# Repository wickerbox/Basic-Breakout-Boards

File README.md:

# Basic-Breakout-Boards

This is a collection of KiCad projects containing breakout boards that will be or have been designed, laid out, assembled, and tested. They are based on wickerlib, so to use them you can grab the <a href="https://github.com/wickerbox/wickerlib">wickerlib</a> symbols and footprints, and you'll be all set.

All the work here is released under the CERN Open Hardware License v1.2.

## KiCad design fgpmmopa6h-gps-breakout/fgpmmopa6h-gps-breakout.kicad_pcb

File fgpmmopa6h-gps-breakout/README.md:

<!--- start title --->
# FGPMMOPA6H GPS Breakout Board v1.1
Simple breakout board for the FGPMMOPA6H GPS module

Updated: 23 Feb 2017

- Author: Jenner Hanni
- Website: http://wickerbox.net
- Company: Wickerbox Electronics
- License: CERN Open Hardware License v1.2

<!--- end title --->

- To use with a 5V FTDI cable, orient cable with RESET (green) at pin 1 on J1.

- To use with 5V controllers, connect VCC, 5V_RX, 5V_TX, and GND.

- To use with 3.3V controllers, connect VCC, 5V_RX, 3.3V_TX, and GND.

1PPS, RTCM, and the FIX are 3.3V-level signals and may not be interpreted correctly by a 5V system.

### Notes on 3.3V/5V compatibility

- Atmega328 provides output signals above 4.2V for HIGH and below 0.9V for LOW. 
- Atmega328 detects input signals above 3V as HIGH and below 1.5V for LOW.
- The FGPMMOPA6H provides output signals 2.0-3.3V for HIGH and 0-0.8V for LOW. 
- The FGPMMOPA6H detects input signals 2.4-3.3V for HIGH and 0-0.4V for LOW.

<!--- bom start --->
### Bill of Materials

|Ref|Qty|Description|Digikey PN|
|---|---|-----------|------|
|AN1|1|CONN UFL JACK STR 50 OHM SMD|H122041-ND|
|BAT1|1|CR1220 BATTERY HOLDER SMT FLATPIN|BK-916-CT-ND|
|C3 C2 C1|3|CAP CER 1UF 10V X7R 0603|1276-1946-1-ND|
|C4|1|CAP CER 0.01UF 50V X7R 0603|490-1512-1-ND|
|D1|1|DIODE GEN PURP 75V 250MA 1N4148 SOD123|1655-1360-1-ND|
|J1|1|HEADER MALE 10POS TH 1x10 0.1”|952-1902-ND|
|LED1|1|LED AMBER DIFFUSED 0603 SMD|475-2712-1-ND|
|R1|1|RES SMD 10K OHM 1% 1/8W 0603|RNCP0603FTD10K0CT-ND|
|R3 R2|2|RES SMD 470 OHM 5% 1/4W 0603|RHM470DCT-ND|
|S1|1|SWITCH TACTILE SPST-NO 0.05A 12V|SW1020CT-ND|
|U1|1|IC REG LDO 3.3V 0.15A SOT353|576-3193-1-ND|

|Ref|Qty|Description|Adafruit PN|
|---|---|-----------|------|
|U2|1|GPS MODULE PA6H MTK3339|790|

<!--- bom end --->

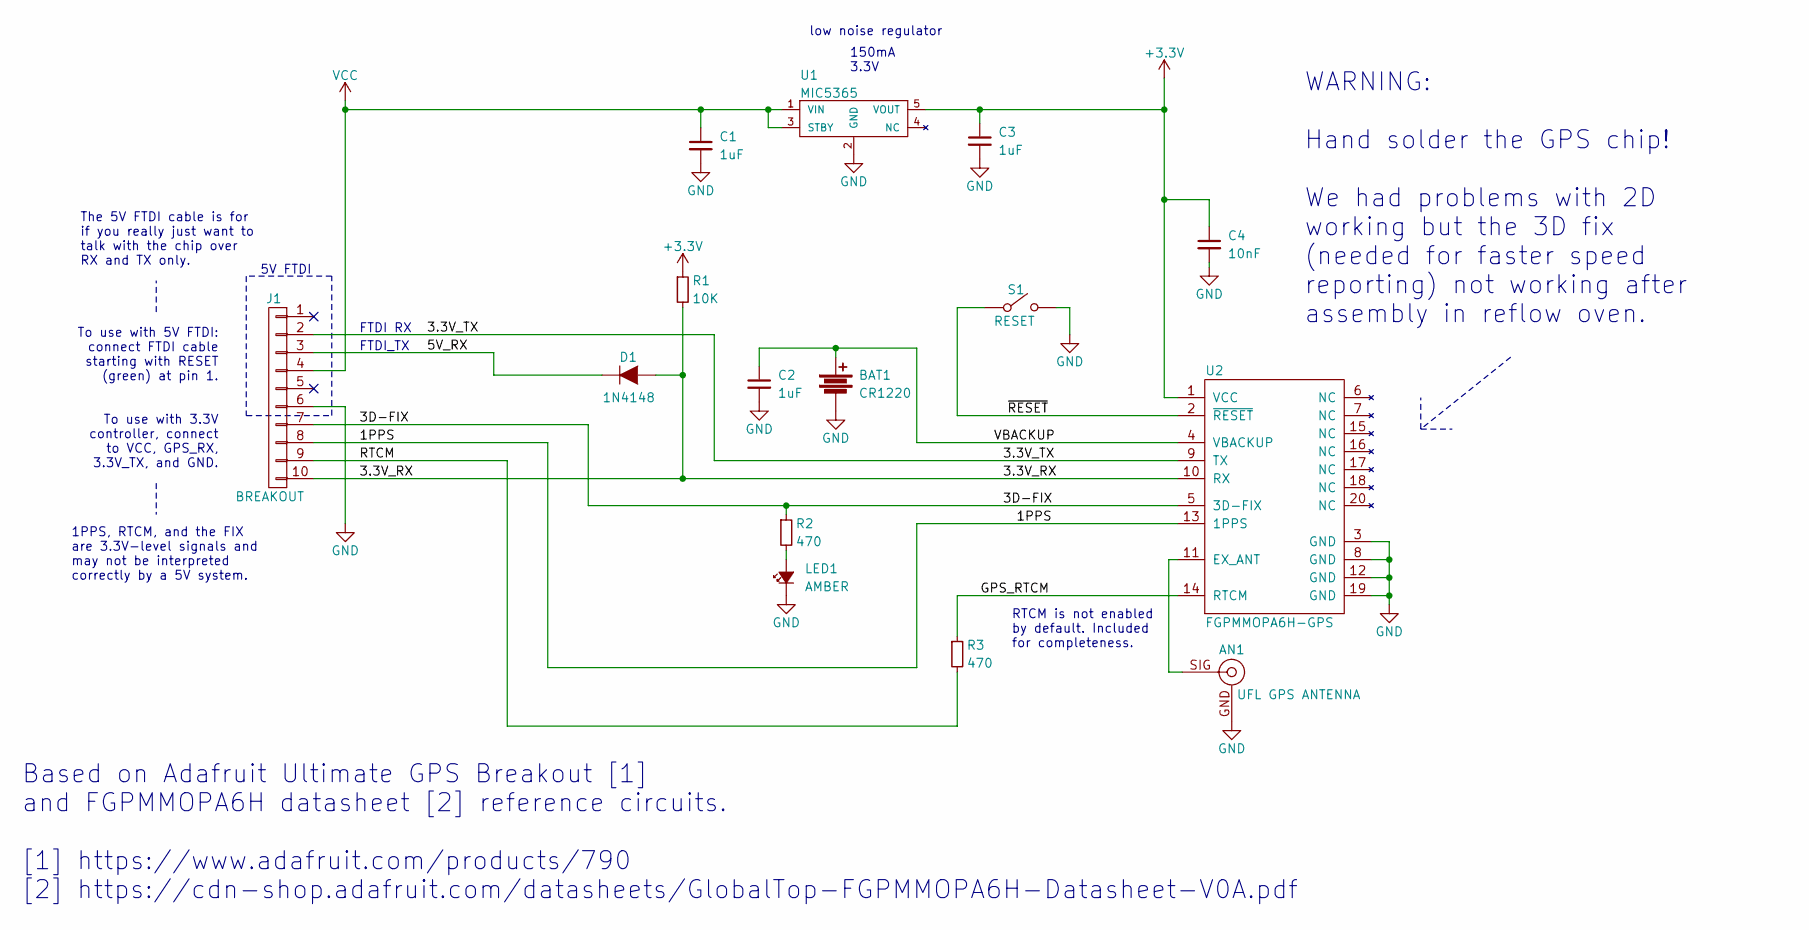
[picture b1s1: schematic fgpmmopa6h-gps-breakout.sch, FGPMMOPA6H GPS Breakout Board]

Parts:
AN1: UFL GPS ANTENNA; U.FL-COAX
BAT1: CR1220; BATT-HOLDER-CR1220-BK-916
C1, C2, C3: 1uF; RLC-0603-SMD
C4: 10nF; RLC-0603-SMD
D1: 1N4148; SOD-123
J1: BREAKOUT; CONN-HEADER-STRAIGHT-P2.54MM-1x10
LED1: AMBER; LED-0603-SMD
R1: 10K; RLC-0603-SMD
R2, R3: 470; RLC-0603-SMD
S1: RESET; SWITCH-OMRON-MOMENTARY-SMD-B3U-1000P
U1: MIC5365; SOT-353
U2: FGPMMOPA6H-GPS; FGPMMOPA6H

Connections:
+3V3: C3.1, C4.1, R1.1, U1.5 (VOUT), U2.1 (VCC)
/1PPS: J1.8, U2.13 (1PPS)
/3.3V_RX: D1.2 (A), J1.10, R1.2, U2.10 (RX)
/3.3V_TX: J1.2, U2.9 (TX)
/3D-FIX: J1.7, R2.1, U2.5 (3D-FIX)
/5V_RX: D1.1 (K), J1.3
/GPS_RTCM: R3.1, U2.14 (RTCM)
/RTCM: J1.9, R3.2
/VBACKUP: BAT1.1, C2.1, U2.4 (VBACKUP)
/~RESET: S1.1, U2.2 (~RESET)
GND: AN1.GND (2), BAT1.GND, C1.2, C2.2, C3.2, C4.2, J1.6, LED1.1 (K), S1.2, U1.2 (GND), U2.3 (GND), U2.8 (GND), U2.12 (GND), U2.19 (GND)
unnamed: AN1.SIG (1), U2.11 (EX_ANT)
unnamed: LED1.2 (A), R2.2
VCC: C1.1, J1.4, U1.1 (VIN), U1.3 (STBY)

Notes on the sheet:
150mA 3.3V
low noise regulator
Based on Adafruit Ultimate GPS Breakout [1] and FGPMMOPA6H datasheet [2] reference circuits. [1] https://www.adafruit.com/products/790 [2] https://cdn-shop.adafruit.com/datasheets/GlobalTop-FGPMMOPA6H-Datasheet-V0A.pdf
To use with 5V FTDI: connect FTDI cable starting with RESET (green) at pin 1. To use with 3.3V controller, connect to VCC, GPS_RX, 3.3V_TX, and GND.
RTCM is not enabled by default. Included for completeness.
1PPS, RTCM, and the FIX are 3.3V-level signals and may not be interpreted correctly by a 5V system.
The 5V FTDI cable is for if you really just want to talk with the chip over RX and TX only.
5V FTDI
FTDI RX
FTDI_TX
WARNING: Hand solder the GPS chip! We had problems with 2D working but the 3D fix (needed for faster speed reporting) not working after assembly in reflow oven.

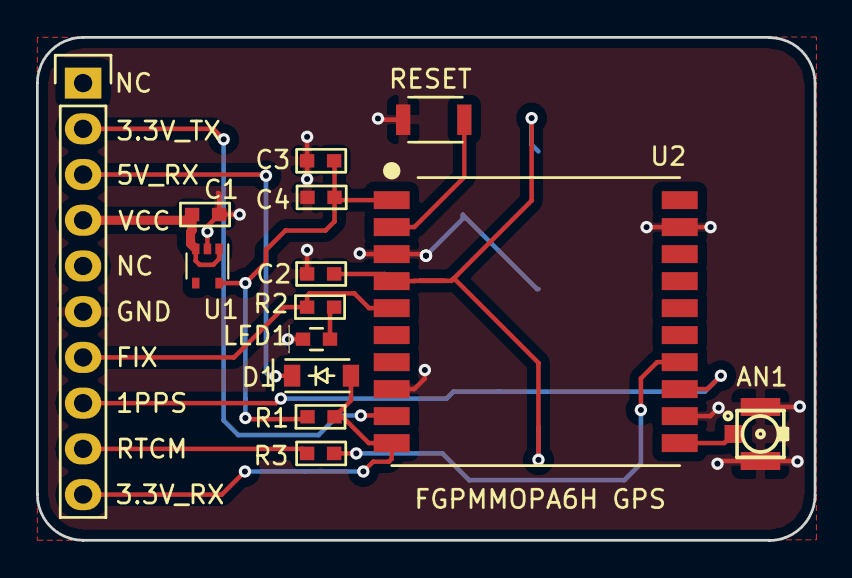
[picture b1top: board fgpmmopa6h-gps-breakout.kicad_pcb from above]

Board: 2 copper layers, 43.2 x 28.0 mm, 15 parts (1 on the bottom side), 14 nets.

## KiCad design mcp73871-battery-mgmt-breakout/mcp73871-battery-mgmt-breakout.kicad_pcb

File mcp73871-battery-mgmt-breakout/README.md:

<!--- start title --->
# MCP73871 Battery Management Breakout Board v1.0
Breakout board for a load-sharing battery/power control chip.

- Updated: 14 Aug 2017
- Author: Jenner Hanni
- Website: http://wickerbox.net
- Company: Wickerbox Electronics
- License: CERN Open Hardware License v1.2
<!--- end title --->

<!--- bom start --->
### Bill of Materials

|Ref|Qty|Description|Digikey PN|
|---|---|-----------|------|
|C1 C2 C3|3|CAP CER 4.7UF 50V X7R 1206|587-2994-1-ND|
|J1|1|USB MICRO-B RECEPTACLE 5PIN SMT R/A STUDS|609-4616-1-ND|
|J2|1|CONN HEADER PH SIDE 2POS 2MM|455-1719-ND|
|J3 J4|2|HEADER FEMALE 7POS TH 1x07 0.1IN|952-1905-ND|
|LED1 LED2 LED3|3|LED AMBER DIFFUSED 0603 SMD|475-2712-1-ND|
|R1|1|RES SMD 0.0 OHM JUMPER 1/8W 0603|MCT0603-0.0-ZZCT-ND|
|R2 R3 R4|3|RES SMD 470 OHM 5% 1/4W 0603|RHM470DCT-ND|
|R5|1|NTC THERMISTOR 10K OHM 1% 0402|445-2550-1-ND|
|R6|1|RES SMD 2K OHM 1% 1/8W 0603|RNCP0603FTD2K00CT-ND|
|R7|1|RES SMD 100K OHM 1% 1/10W 0603|RMCF0603FG100KCT-ND|
|U1|1|IC USB/AC BATT CHRGR MCP73871 20QFN|MCP73871T-2CCI/MLCT-ND|

|Ref|Qty|Description|Adafruit PN|
|---|---|-----------|------|
|B1|1|Lithium Ion Polymer Battery - 3.7v 500mAh|1578|

<!--- bom end --->
<!--- assy start --->
### Assembly Info for Quoting

<!--- assy end --->

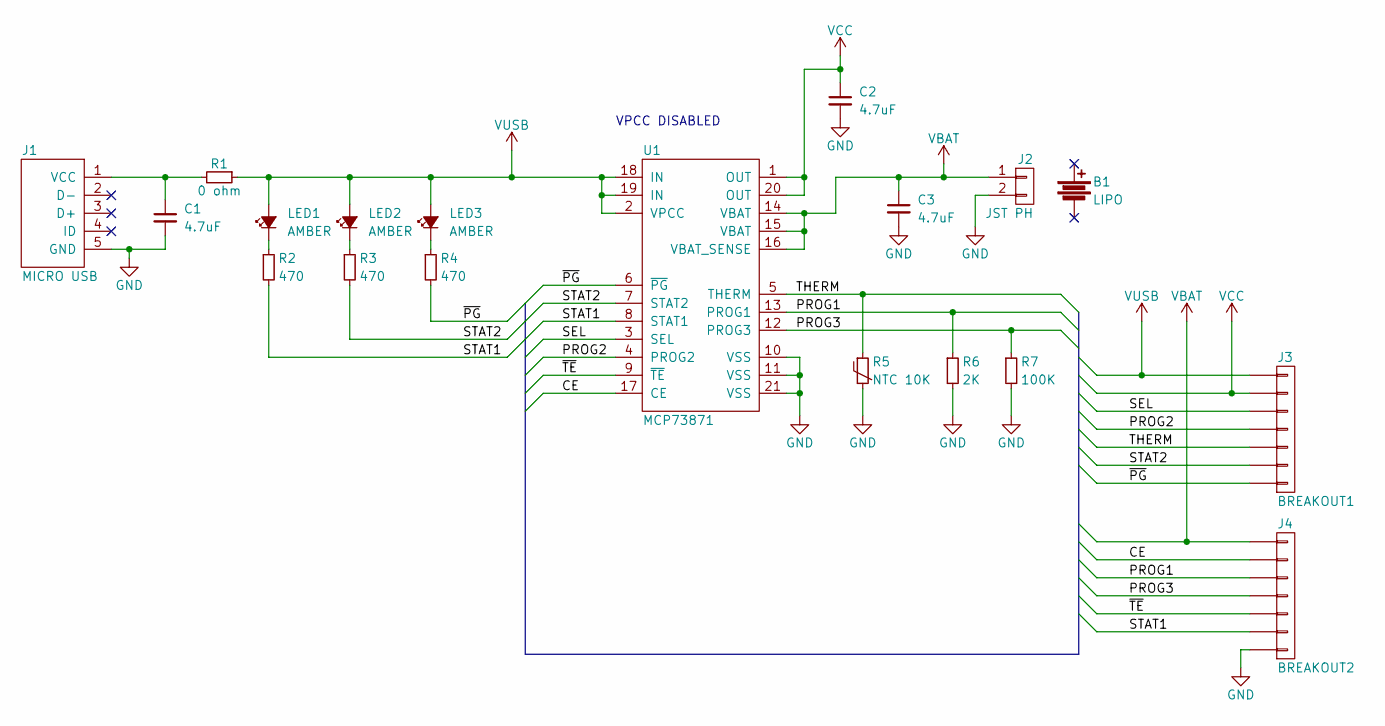
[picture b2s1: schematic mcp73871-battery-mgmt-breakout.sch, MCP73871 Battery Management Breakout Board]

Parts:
B1: LIPO; UNDEFINED
C1, C2, C3: 4.7uF; RLC-1206-SMD
J1: MICRO USB; CONN-USB-MICRO-B-AMPHENOL-10118193-0001LF
J2: JST PH; CONN-JST-S2B-PH-SM4-TB
J3: BREAKOUT1; CONN-HEADER-STRAIGHT-P2.54MM-1x07
J4: BREAKOUT2; CONN-HEADER-STRAIGHT-P2.54MM-1x07
LED1, LED2, LED3: AMBER; LED-0603-SMD
R1: 0 ohm; RLC-0603-SMD
R2, R3, R4: 470; RLC-0603-SMD
R5: NTC 10K; RLC-0402-SMD
R6: 2K; RLC-0603-SMD
R7: 100K; RLC-0603-SMD
U1: MCP73871; QFN-20-1EP-4x4MM_P0.5MM

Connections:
/CE: J4.2, U1.17 (CE)
/PROG1: J4.3, R6.1, U1.13 (PROG1)
/PROG2: J3.4, U1.4 (PROG2)
/PROG3: J4.4, R7.1, U1.12 (PROG3)
/SEL: J3.3, U1.3 (SEL)
/STAT1: J4.6, R2.2, U1.8 (STAT1)
/STAT2: J3.6, R3.2, U1.7 (STAT2)
/THERM: J3.5, R5.1, U1.5 (THERM)
/~PG: J3.7, R4.2, U1.6 (~PG)
/~TE: J4.5, U1.9 (~TE)
GND: C1.2, C2.2, C3.2, J1.5 (GND), J2.2, J4.7, R5.2, R6.2, R7.2, U1.10 (VSS), U1.11 (VSS), U1.21 (VSS)
unnamed: C1.1, J1.1 (VCC), R1.2
unnamed: LED1.1 (K), R2.1
unnamed: LED2.1 (K), R3.1
unnamed: LED3.1 (K), R4.1
VBAT: C3.1, J2.1, J4.1, U1.14 (VBAT), U1.15 (VBAT), U1.16 (VBAT_SENSE)
VCC: C2.1, J3.2, U1.1 (OUT), U1.20 (OUT)
VUSB: J3.1, LED1.2 (A), LED2.2 (A), LED3.2 (A), R1.1, U1.2 (VPCC), U1.18 (IN), U1.19 (IN)

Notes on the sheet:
VPCC DISABLED

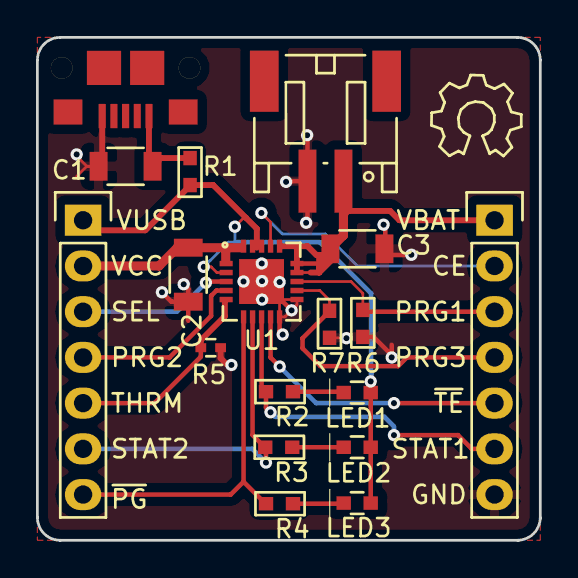
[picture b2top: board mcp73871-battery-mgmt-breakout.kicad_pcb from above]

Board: 2 copper layers, 27.9 x 27.9 mm, 18 parts (0 on the bottom side), 18 nets.

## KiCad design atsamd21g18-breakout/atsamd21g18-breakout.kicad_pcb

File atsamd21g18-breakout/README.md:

<!--- start title --->
# ATSAMD21G18 Cortex M0 Breakout Board v1.0
Arduino-compatible, breadboard-compatible with onboard uSD and RTC.

- Updated: 14 Aug 2017

- Author: Jenner Hanni
- Website: http://wickerbox.net
- Company: Wickerbox Electronics
- License: CERN Open Hardware License v1.2
<!--- end title --->

Comes with a 5-pin SWD programming interface so the bootloader can be flashed using an STLink v2 and [adalink](https://github.com/adafruit/Adafruit_Adalink).

<!--- bom start --->
### Bill of Materials

|Ref|Qty|Description|Digikey PN|
|---|---|-----------|------|
|C1 C2 C5|3|CAP CER 1UF 25V X7R 0603|587-2984-1-ND|
|C10 C11 C4 C7 C9|5|CAP CER 0.1UF 100V X7R 0603|490-3285-1-ND|
|C3|1|CAP CER 10UF 16V X7R 0805|1276-2872-1-ND|
|C6 C8|2|CAP CER 22pF 50V NP0 0603|399-9031-1-ND|
|D1 D3|2|VARISTOR ESD PROTECT USB|CG0603MLC-05ECT-ND|
|D2|1|DIODE SCHOTTKY 20V 1A SMA|SS12-E3/61TGICT-ND|
|J1|1|HEADER MALE 5POS TH 1x05 0.1IN|952-1902-ND|
|J2|1|USB MICRO-B RECEPTACLE 5PIN SMT R/A STUDS|609-4616-1-ND|
|J3 J4|2|HEADER FEMALE 18POS TH 1x18 0.1IN|952-1905-ND|
|L1 L2 L3|3|FERRITE BEAD 30 OHM 0805 1LN|MH2029-300YCT-ND|
|R1|1|RES SMD 1K OHM 1% 1/10W 0603|1276-3484-1-ND|
|R2|1|RES SMD 10K OHM 1% 1/8W 0603|RNCP0603FTD10K0CT-ND|
|R3|1|RES SMD 330 OHM 5% 1/10W 0603|311-330GRCT-ND|
|S1|1|SWITCH TACTILE SPST-NO 0.05A 12V|SW1020CT-ND|
|U1|1|IC REG LDO 3.3V 0.5A BU33SD5WG 5SSOP|BU33SD5WG-TRCT-ND|
|U2|1|IC MCU 32BIT 256KB FLASH ATSAMD21G 48TQFP|ATSAMD21G18A-AUTCT-ND|
|X1|1|CRYSTAL 16MHZ 30PPM 18pF 4SMD|CTX1206CT-ND|

<!--- bom end --->

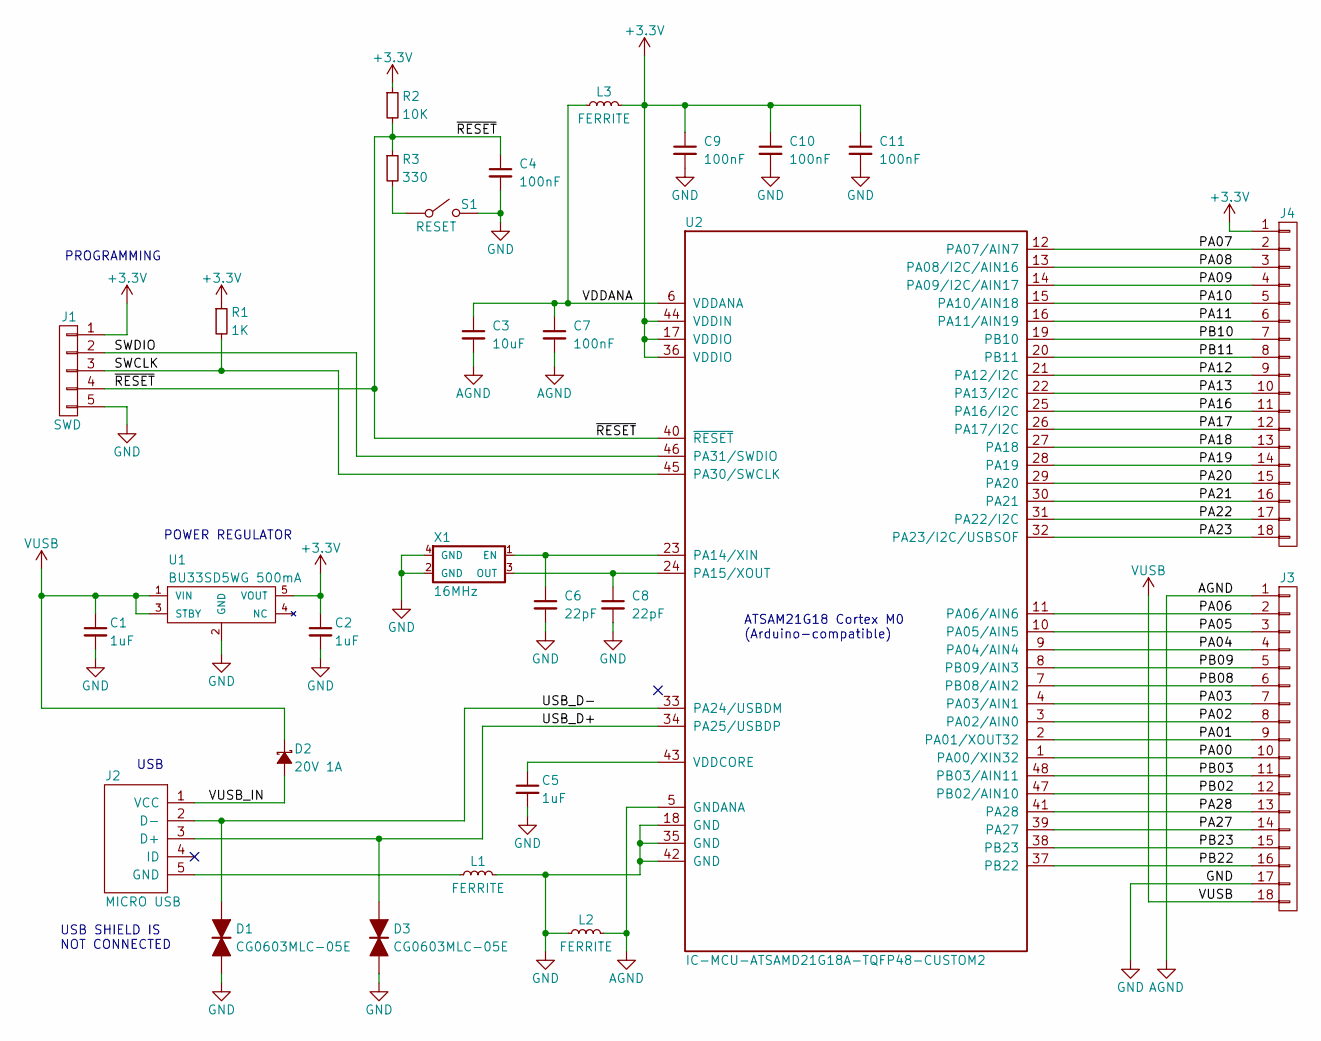
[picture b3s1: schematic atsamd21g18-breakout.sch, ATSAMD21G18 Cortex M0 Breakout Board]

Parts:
C1, C2, C5: 1uF; RLC-0603-SMD
C3: 10uF; RLC-0805-SMD
C4, C7, C9, C10, C11: 100nF; RLC-0603-SMD
C6, C8: 22pF; RLC-0603-SMD
D1, D3: CG0603MLC-05E; RLC-0603-SMD
D2: 20V 1A; DIODE-SMA
J1: SWD; CONN-HEADER-STRAIGHT-P2.54MM-1x05
J2: MICRO USB; CONN-USB-MICRO-B-AMPHENOL-10118193-0001LF
J3, J4: HEADER-FEMALE-18POS-TH-1x18-P0.1IN; CONN-HEADER-STRAIGHT-P2.54MM-1x18
L1, L2, L3: FERRITE; RLC-0805-SMD
R1: 1K; RLC-0603-SMD
R2: 10K; RLC-0603-SMD
R3: 330; RLC-0603-SMD
S1: RESET; SWITCH-OMRON-MOMENTARY-SMD-B3U-1000P
U1: BU33SD5WG 500mA; SSOP-5
U2: IC-MCU-ATSAMD21G18A-TQFP48-CUSTOM2; TQFP-48_7x7mm_Pitch0.5mm
X1: 16MHz; CRYSTAL-CTS-4SMD

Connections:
+3V3: C2.1, C9.1, C10.1, C11.1, J1.1, J4.1, L3.2, R1.1, R2.1, U1.5 (VOUT), U2.17 (VDDIO), U2.36 (VDDIO), U2.44 (VDDIN)
/PA00: J3.10, U2.1 (PA00/XIN32)
/PA01: J3.9, U2.2 (PA01/XOUT32)
/PA02: J3.8, U2.3 (PA02/AIN0)
/PA03: J3.7, U2.4 (PA03/AIN1)
/PA04: J3.4, U2.9 (PA04/AIN4)
/PA05: J3.3, U2.10 (PA05/AIN5)
/PA06: J3.2, U2.11 (PA06/AIN6)
/PA07: J4.2, U2.12 (PA07/AIN7)
/PA08: J4.3, U2.13 (PA08/I2C/AIN16)
/PA09: J4.4, U2.14 (PA09/I2C/AIN17)
/PA10: J4.5, U2.15 (PA10/AIN18)
/PA11: J4.6, U2.16 (PA11/AIN19)
/PA12: J4.9, U2.21 (PA12/I2C)
/PA13: J4.10, U2.22 (PA13/I2C)
/PA16: J4.11, U2.25 (PA16/I2C)
/PA17: J4.12, U2.26 (PA17/I2C)
/PA18: J4.13, U2.27 (PA18)
/PA19: J4.14, U2.28 (PA19)
/PA20: J4.15, U2.29 (PA20)
/PA21: J4.16, U2.30 (PA21)
/PA22: J4.17, U2.31 (PA22/I2C)
/PA23: J4.18, U2.32 (PA23/I2C/USBSOF)
/PA27: J3.14, U2.39 (PA27)
/PA28: J3.13, U2.41 (PA28)
/PB02: J3.12, U2.47 (PB02/AIN10)
/PB03: J3.11, U2.48 (PB03/AIN11)
/PB08: J3.6, U2.7 (PB08/AIN2)
/PB09: J3.5, U2.8 (PB09/AIN3)
/PB10: J4.7, U2.19 (PB10)
/PB11: J4.8, U2.20 (PB11)
/PB22: J3.16, U2.37 (PB22)
/PB23: J3.15, U2.38 (PB23)
/SWCLK: J1.3, R1.2, U2.45 (PA30/SWCLK)
/SWDIO: J1.2, U2.46 (PA31/SWDIO)
/USB_D+: D3.1, J2.3 (D+), U2.34 (PA25/USBDP)
/USB_D-: D1.1, J2.2 (D-), U2.33 (PA24/USBDM)
/VDDANA: C3.1, C7.1, L3.1, U2.6 (VDDANA)
/VUSB_IN: D2.2 (A), J2.1 (VCC)
/~RESET: C4.1, J1.4, R2.2, R3.1, U2.40 (~RESET)
AGND: C3.2, C7.2, J3.1, L2.2, U2.5 (GNDANA)
GND: C1.2, C2.2, C4.2, C5.2, C6.2, C8.2, C9.2, C10.2, C11.2, D1.2, D3.2, J1.5, J3.17, L1.2, L2.1, S1.2, U1.2 (GND), U2.18 (GND), U2.35 (GND), U2.42 (GND), X1.2 (GND), X1.4 (GND)
unnamed: C5.1, U2.43 (VDDCORE)
unnamed: C6.1, U2.23 (PA14/XIN), X1.1 (EN)
unnamed: C8.1, U2.24 (PA15/XOUT), X1.3 (OUT)
unnamed: J2.5 (GND), L1.1
unnamed: R3.2, S1.1
VUSB: C1.1, D2.1 (K), J3.18, U1.1 (VIN), U1.3 (STBY)

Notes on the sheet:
ATSAM21G18 Cortex M0 (Arduino-compatible)
PROGRAMMING
POWER REGULATOR
USB
USB SHIELD IS NOT CONNECTED

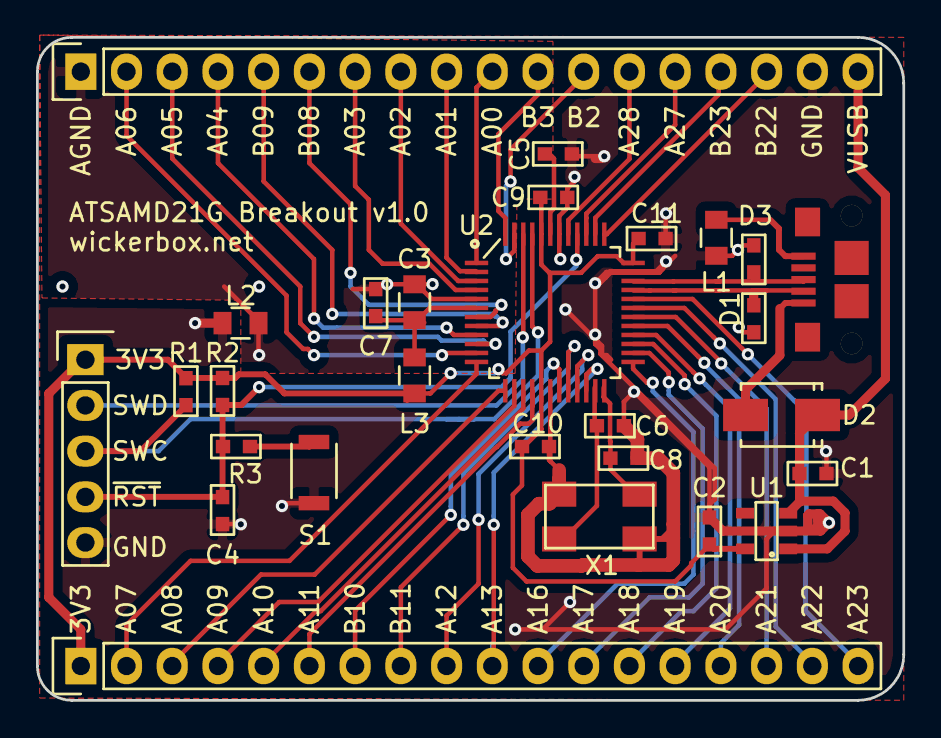
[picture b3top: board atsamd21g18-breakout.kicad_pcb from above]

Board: 2 copper layers, 48.1 x 36.8 mm, 28 parts (0 on the bottom side), 48 nets.

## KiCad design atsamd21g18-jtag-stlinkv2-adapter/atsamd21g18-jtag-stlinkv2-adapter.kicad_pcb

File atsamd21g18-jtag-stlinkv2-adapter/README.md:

<!--- start title --->
# ATSAMD21G18-STLinkv2 JTAG Adapter Board v1.0
Converts 20-pin giant JTAG connector into 1.27mm-pitch 2x5 connector.

- Updated: 14 Aug 2017

- Author: Jenner Hanni
- Website: http://wickerbox.net
- Company: Wickerbox Electronics
- License: CERN Open Hardware License v1.2
<!--- end title --->

Description.

<!--- bom start --->
### Bill of Materials

|Ref|Qty|Description|Digikey PN|
|---|---|-----------|------|
|J1|1|HEADER MALE 20POS TH 2x10 0.1IN KEY|ED10524-ND|
|J2|1|HEADER MALE SHROUDED 10POS 2x5 0.1IN KEY JTAG|30310-6002HB-ND|
|J3|1|HEADER MALE 5POS TH 1x05 0.1IN|952-1902-ND|
|J4|1|HEADER MALE SHROUDED 10POS 2x5 0.27MM KEY|1175-1627-ND|

<!--- bom end --->

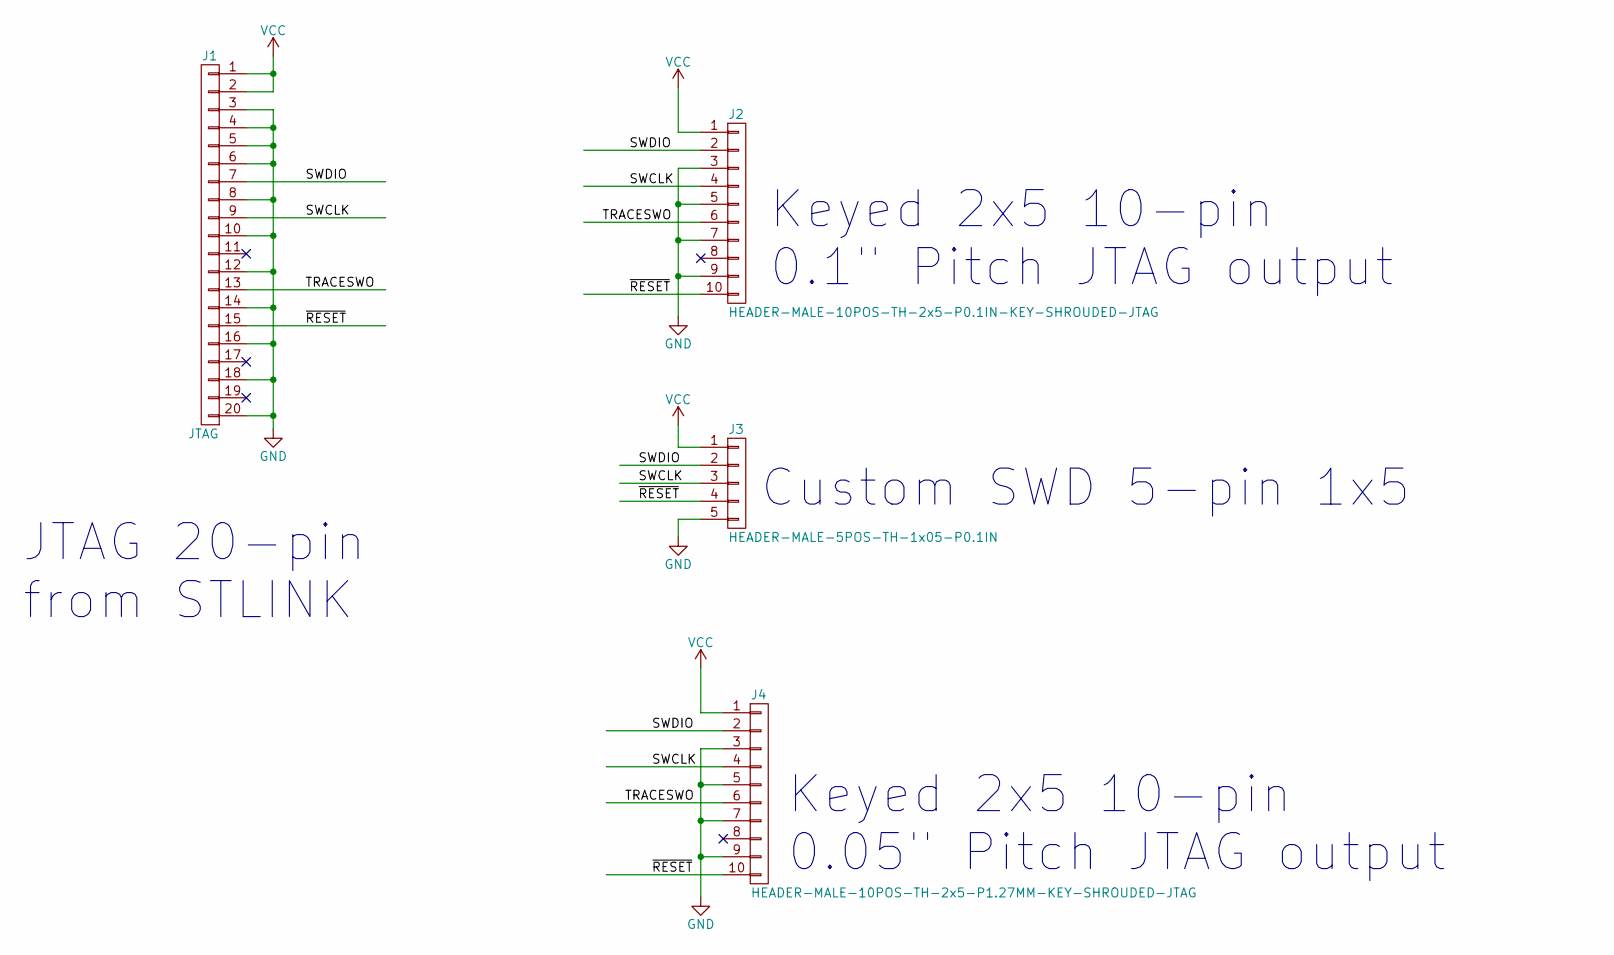
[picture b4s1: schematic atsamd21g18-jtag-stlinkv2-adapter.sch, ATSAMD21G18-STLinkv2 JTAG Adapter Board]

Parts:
J1: JTAG; CONN-ONSHORE-JTAG-2x10-2.54MMP
J2: HEADER-MALE-10POS-TH-2x5-P0.1IN-KEY-SHROUDED-JTAG; CONN-3M-JTAG-2x05-2.54MMP
J3: HEADER-MALE-5POS-TH-1x05-P0.1IN; CONN-HEADER-STRAIGHT-P2.54MM-1x05
J4: HEADER-MALE-10POS-TH-2x5-P1.27MM-KEY-SHROUDED-JTAG; CONN-ONSHORE-JTAG-2x05-1.27MMP

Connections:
/SWCLK: J1.9, J2.4, J3.3, J4.4
/SWDIO: J1.7, J2.2, J3.2, J4.2
/TRACESWO: J1.13, J2.6, J4.6
/~RESET: J1.15, J2.10, J3.4, J4.10
GND: J1.3, J1.4, J1.5, J1.6, J1.8, J1.10, J1.12, J1.14, J1.16, J1.18, J1.20, J2.3, J2.5, J2.7, J2.9, J3.5, J4.3, J4.5, J4.7, J4.9
VCC: J1.1, J1.2, J2.1, J3.1, J4.1

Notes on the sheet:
JTAG 20-pin from STLINK
Keyed 2x5 10-pin 0.1" Pitch JTAG output
Custom SWD 5-pin 1x5
Keyed 2x5 10-pin 0.05" Pitch JTAG output

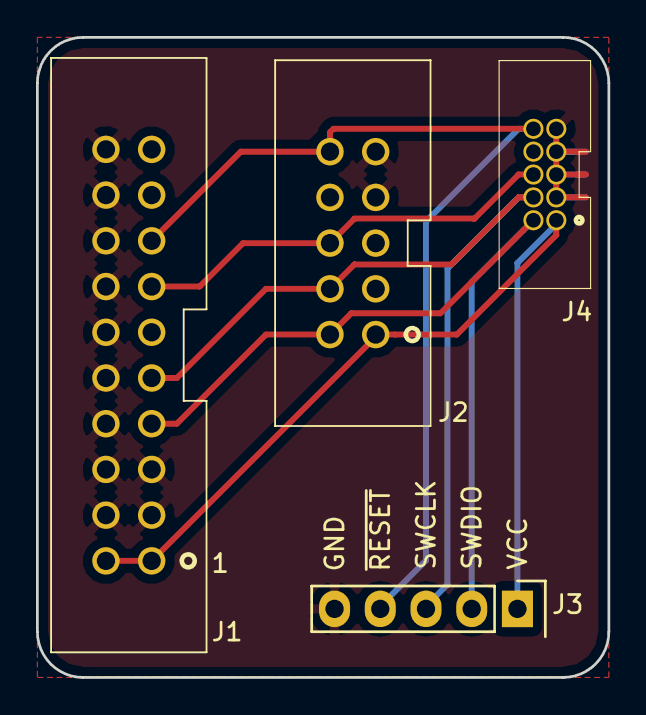
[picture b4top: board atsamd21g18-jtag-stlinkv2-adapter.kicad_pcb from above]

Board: 2 copper layers, 31.8 x 35.6 mm, 4 parts (0 on the bottom side), 6 nets.

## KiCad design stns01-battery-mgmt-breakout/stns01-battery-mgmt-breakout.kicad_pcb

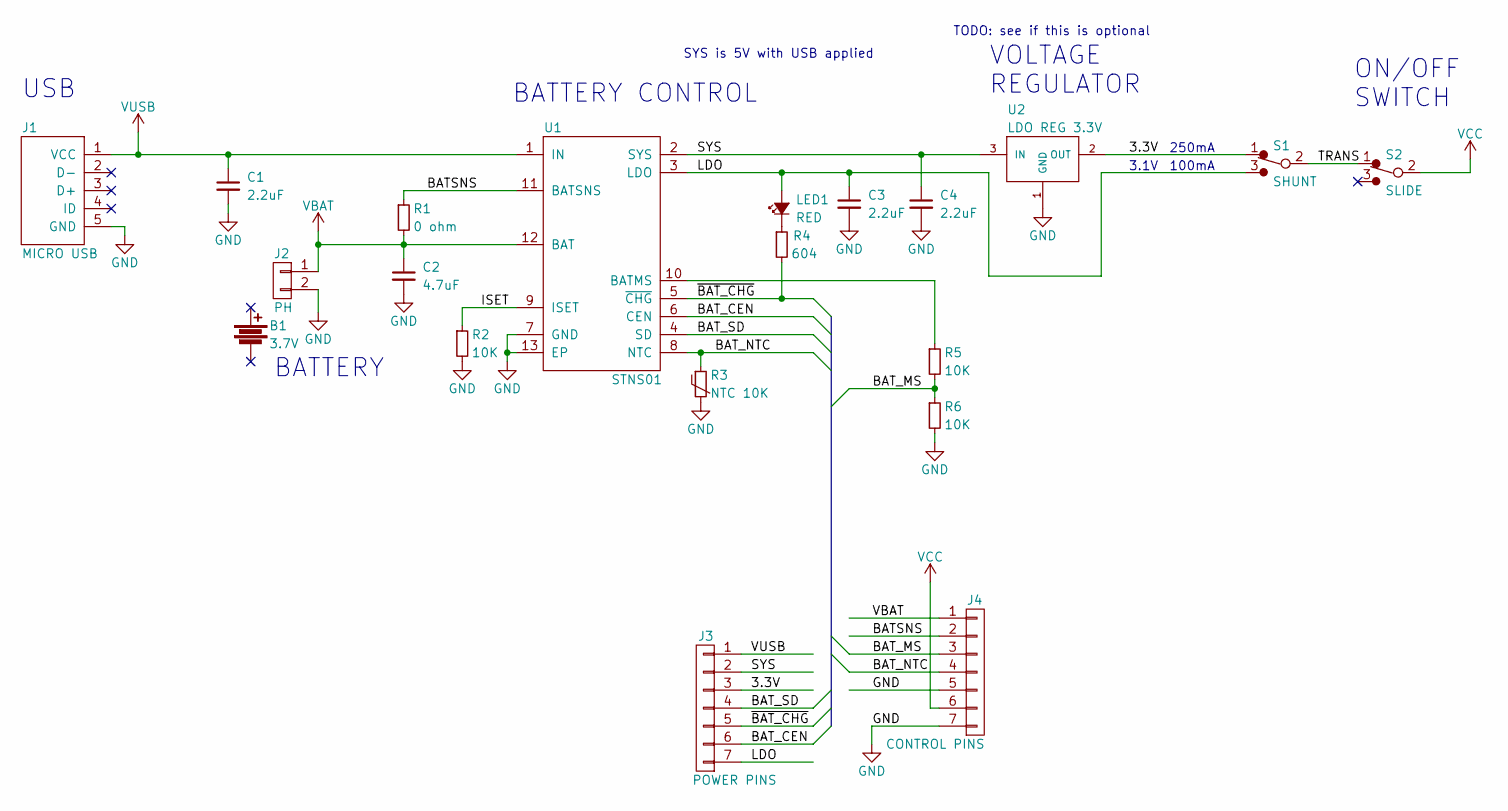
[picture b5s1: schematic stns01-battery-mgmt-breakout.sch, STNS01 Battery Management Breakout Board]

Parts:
B1: 3.7V; UNDEFINED
C1, C3, C4: 2.2uF; RLC-0603-SMD
C2: 4.7uF; RLC-0603-SMD
J1: MICRO USB; CONN-USB-MICRO-B-AMPHENOL-10118193-0001LF
J2: PH; CONN-JST-S2B-PH-SM4-TB
J3: POWER PINS; CONN-HEADER-STRAIGHT-P2.54MM-1x07
J4: CONTROL PINS; CONN-HEADER-STRAIGHT-P2.54MM-1x07
LED1: RED; LED-0603-SMD
R1: 0 ohm; RLC-0603-SMD
R2, R5, R6: 10K; RLC-0603-SMD
R3: NTC 10K; RLC-0603-SMD
R4: 604; RLC-0603-SMD
S1: SHUNT; CONN-HEADER-STRAIGHT-P2.54MM-1x03
S2: SLIDE; SWITCH-ESWITCH-SLIDE-TH-EG1218
U1: STNS01; DFN-12-1EP-3x3MM-P0.45MM
U2: LDO REG 3.3V; SOT-23-3

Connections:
/3.3V: J3.3, S1.1, U2.2 (OUT)
/BATSNS: J4.2, R1.1, U1.11 (BATSNS)
/BAT_CEN: J3.6, U1.6 (CEN)
/BAT_MS: J4.3, R5.2, R6.1
/BAT_NTC: J4.4, R3.1, U1.8 (NTC)
/BAT_SD: J3.4, U1.4 (SD)
/ISET: R2.1, U1.9 (ISET)
/LDO: C3.1, J3.7, LED1.2 (A), S1.3, U1.3 (LDO)
/SYS: C4.1, J3.2, U1.2 (SYS), U2.3 (IN)
/TRANS: S1.2, S2.1
/~BAT_CHG: J3.5, R4.2, U1.5 (~CHG)
GND: C1.2, C2.2, C3.2, C4.2, J1.5 (GND), J2.2, J4.5, J4.7, R2.2, R3.2, R6.2, U1.7 (GND), U1.13 (EP), U2.1 (GND)
unnamed: LED1.1 (K), R4.1
unnamed: R5.1, U1.10 (BATMS)
VBAT: C2.1, J2.1, J4.1, R1.2, U1.12 (BAT)
VCC: J4.6, S2.2
VUSB: C1.1, J1.1 (VCC), J3.1, U1.1 (IN)

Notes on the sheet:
BATTERY CONTROL
VOLTAGE REGULATOR
USB
250mA
100mA
BATTERY
SYS is 5V with USB applied
ON/OFF SWITCH
3.1V
TODO: see if this is optional

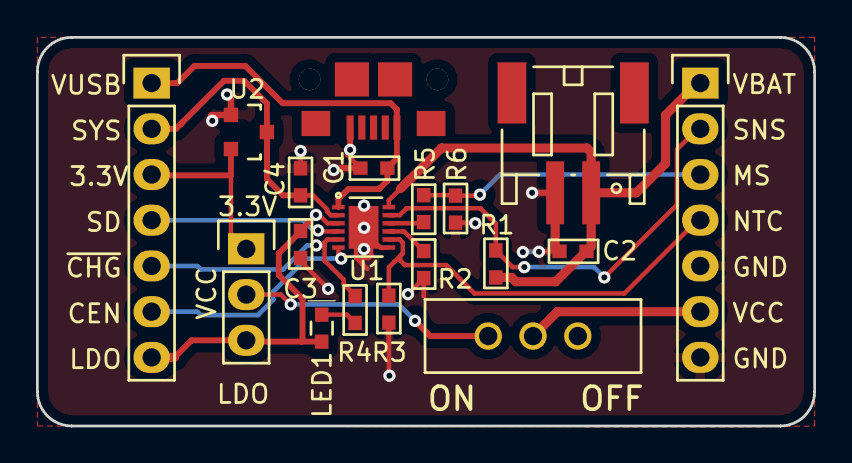
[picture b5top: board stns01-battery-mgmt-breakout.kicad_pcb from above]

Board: 2 copper layers, 43.2 x 21.6 mm, 19 parts (0 on the bottom side), 17 nets.

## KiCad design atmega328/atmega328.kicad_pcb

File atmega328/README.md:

<!--- start title --->
# Basic Atmega328 Breakout Board v1.2

This is a breakout board for the Atmega328. It supports input voltage up to 16V, regulating down to 5V for the microcontroller. A bootloader can be loaded over ICSP and then the board can be powered and communicated with over an FTDI cable. All the input/output pins are broken out for prototyping.

Updated: 31 Dec 2016

- Author: Jenner Hanni
- Website: http://wickerbox.net
- Company: Wickerbox Electronics
- License: CERN Open Hardware License v1.2
<!--- end title --->

The project is released as open hardware under the CERN v1.2 Open Hardware license.

<!--- start title --->
The project uses the Atmega328 template from [wickerlib](http://wickerbox.net/wickerlib).

You can order a set of three bare boards for $13.35 from OSH Park [here](https://oshpark.com/shared_projects/Bx0lZ6cN).
<!--- end title --->

### Bill of Materials

<!--- bom start --->
### Bill of Materials

|Ref|Qty|Description|Digikey PN|
|---|---|-----------|------|
|C2 C6|2|CAP CER 10UF 25V X7R 1210|587-2599-1-ND|
|C3 C4|2|CAP CER 22pF 100V C0G NP0 0603|399-11145-1-ND|
|C7 C8 C9 C1 C5|5|CAP CER 0.1UF 100V X7R 0603|490-3285-1-ND|
|D1|1|TVS DIODE 14VWM 23.2VC SMAJ14A-13-F SMA|SMAJ14A-FDICT-ND|
|D2 D3|2|DIODE SCHOTTKY 20V 1A SMA|SS12-E3/61TGICT-ND|
|F1|1|RESETTABLE FUSE 1.1A 25V MF-MSMF|MF-MSMF110/24X-2CT-ND|
|J1|1|CONN TERM SCREW GREEN 2.54MM 2POS TH|ED10561-ND|
|J2|1|HEADER MALE 6POS TH 1x06 0.1”|952-1902-ND|
|J3|1|HEADER MALE 6POS 2x3 0.1”|952-1921-ND|
|J4 J5|2|HEADER FEMALE 12POS TH 1x12 0.1”|952-1905-ND|
|JP1|1|SHUNT JUMPER 0.1IN BLACK GOLD|3M9580-ND|
|LED1|1|LED AMBER DIFFUSED 0603 SMD|475-2712-1-ND|
|R1|1|RES SMD 10K OHM 5% 1/8W 0805|311-10KARCT-ND|
|R2|1|RES SMD 220 OHM 5% 1/10W 0603|311-22GRCT-ND|
|S1|1|SWITCH TACTILE SPST-NO 0.05A 12V|SW1020CT-ND|
|U1|1|IC REG LDO 5V 1.1A NCP1117 DPAK| NCP1117DT50GOS-ND|
|U2|1|IC MCU 8BIT 32KB FLASH 32TQFP|ATMEGA328P-AU-ND|
|X1|1|CRYSTAL 16MHz 18pF 40 OHM 4SMD|CTX1206CT-ND|

<!--- bom end --->

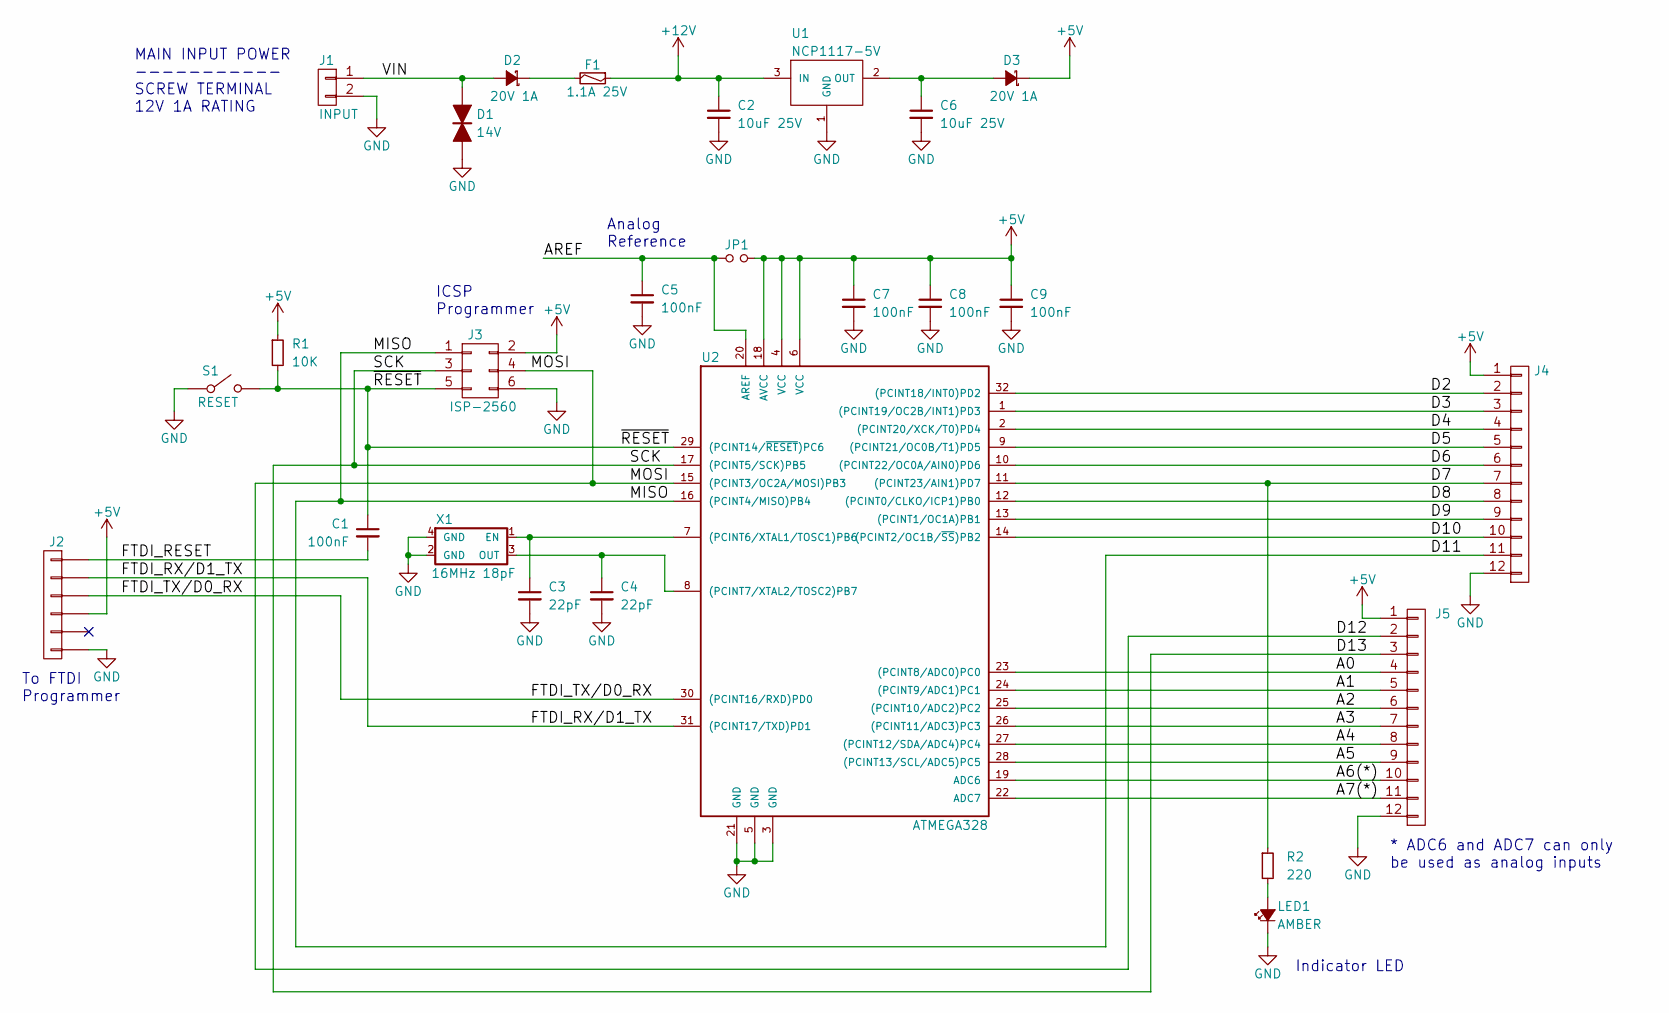
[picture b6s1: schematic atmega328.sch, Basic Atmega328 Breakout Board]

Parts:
C1, C5, C7, C8, C9: 100nF; RLC-0603-SMD
C2, C6: 10uF 25V; RLC-1210-SMD
C3, C4: 22pF; RLC-0603-SMD
D1: 14V; DIODE-SMA
D2, D3: 20V 1A; DIODE-SMA
F1: 1.1A 25V; RLC-1812-SMD
J1: INPUT; CONN-ONSHORE-SCREW-GREEN-2PIN-TH
J2: FTDI; CONN-HEADER-STRAIGHT-P2.54MM-1x06
J3: ISP-2560; CONN-HEADER-STRAIGHT-P2.54MM-2x03
J4, J5: HEADER-FEMALE-12POS-TH-1x12-P0.1IN; CONN-HEADER-STRAIGHT-P2.54MM-1x12
JP1: JUMP; CONN-HEADER-STRAIGHT-P2.54MM-1x02
LED1: AMBER; RLC-0603-SMD
R1: 10K; RLC-0805-SMD
R2: 220; RLC-0603-SMD
S1: RESET; SWITCH-OMRON-MOMENTARY-SMD-B3U-1000P
U1: NCP1117-5V; DPAK
U2: ATMEGA328; TQFP-32-7x7MM-P0.8MM
X1: 16MHz 18pF; CRYSTAL-CTS-4SMD

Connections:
+5V: C7.1, C8.1, C9.1, D3.1 (K), J2.4, J3.2, J4.1, J5.1, JP1.2, R1.1, U2.4 (VCC), U2.6 (VCC), U2.18 (AVCC)
+12V: C2.1, F1.1, U1.3 (IN)
/A0: J5.4, U2.23 ((PCINT8/ADC0)PC0)
/A1: J5.5, U2.24 ((PCINT9/ADC1)PC1)
/A2: J5.6, U2.25 ((PCINT10/ADC2)PC2)
/A3: J5.7, U2.26 ((PCINT11/ADC3)PC3)
/A4: J5.8, U2.27 ((PCINT12/SDA/ADC4)PC4)
/A5: J5.9, U2.28 ((PCINT13/SCL/ADC5)PC5)
/A6(*): J5.10, U2.19 (ADC6)
/A7(*): J5.11, U2.22 (ADC7)
/AREF: C5.1, JP1.1, U2.20 (AREF)
/D2: J4.2, U2.32 ((PCINT18/INT0)PD2)
/D3: J4.3, U2.1 ((PCINT19/OC2B/INT1)PD3)
/D4: J4.4, U2.2 ((PCINT20/XCK/T0)PD4)
/D5: J4.5, U2.9 ((PCINT21/OC0B/T1)PD5)
/D6: J4.6, U2.10 ((PCINT22/OC0A/AIN0)PD6)
/D7: J4.7, R2.1, U2.11 ((PCINT23/AIN1)PD7)
/D8: J4.8, U2.12 ((PCINT0/CLKO/ICP1)PB0)
/D9: J4.9, U2.13 ((PCINT1/OC1A)PB1)
/D10: J4.10, U2.14 ((PCINT2/OC1B/~SS~)PB2)
/D11: J3.1, J4.11, U2.16 ((PCINT4/MISO)PB4)
/D12: J3.4, J5.2, U2.15 ((PCINT3/OC2A/MOSI)PB3)
/D13: J3.3, J5.3, U2.17 ((PCINT5/SCK)PB5)
/FTDI_RESET: C1.2, J2.1
/FTDI_RX/D1_TX: J2.2, U2.31 ((PCINT17/TXD)PD1)
/FTDI_TX/D0_RX: J2.3, U2.30 ((PCINT16/RXD)PD0)
/VIN: D1.1, D2.2 (A), J1.1
/~RESET: C1.1, J3.5, R1.2, S1.2, U2.29 ((PCINT14/~RESET~)PC6)
GND: C2.2, C3.2, C4.2, C5.2, C6.2, C7.2, C8.2, C9.2, D1.2, J1.2, J2.6, J3.6, J4.12, J5.12, LED1.1 (K), S1.1, U1.1 (GND), U2.3 (GND), U2.5 (GND), U2.21 (GND), X1.2 (GND), X1.4 (GND)
unnamed: C3.1, U2.7 ((PCINT6/XTAL1/TOSC1)PB6), X1.1 (EN)
unnamed: C4.1, U2.8 ((PCINT7/XTAL2/TOSC2)PB7), X1.3 (OUT)
unnamed: C6.1, D3.2 (A), U1.2 (OUT)
unnamed: D2.1 (K), F1.2
unnamed: LED1.2 (A), R2.2

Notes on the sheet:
Indicator LED
* ADC6 and ADC7 can only be used as analog inputs
Analog Reference
ICSP Programmer
To FTDI Programmer
MAIN INPUT POWER ----------- SCREW TERMINAL 12V 1A RATING

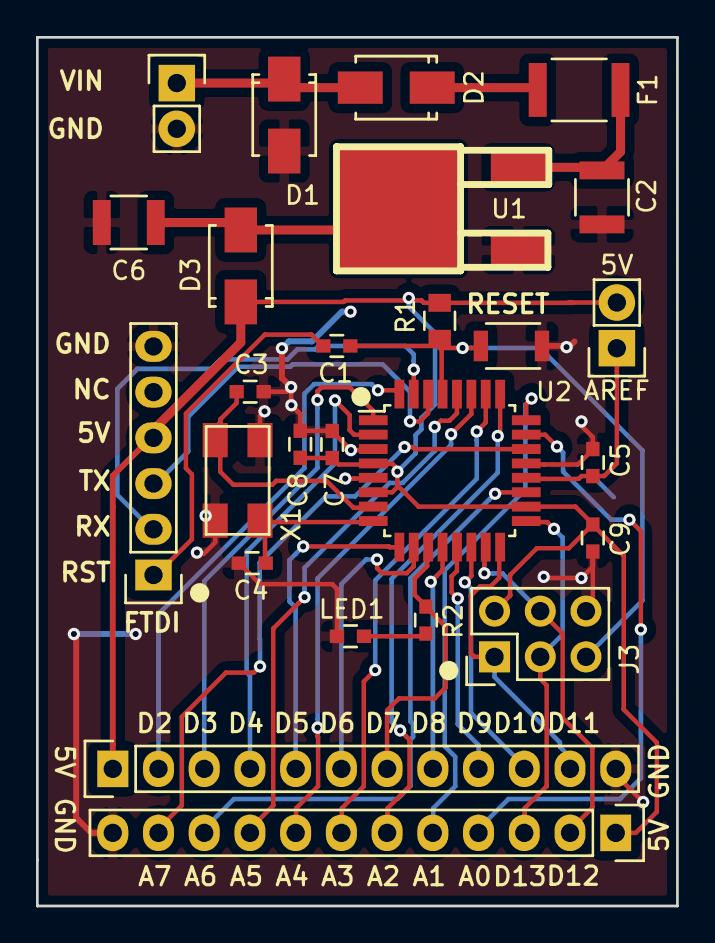
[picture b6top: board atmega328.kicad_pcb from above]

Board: 2 copper layers, 35.6 x 48.3 mm, 26 parts (0 on the bottom side), 34 nets.

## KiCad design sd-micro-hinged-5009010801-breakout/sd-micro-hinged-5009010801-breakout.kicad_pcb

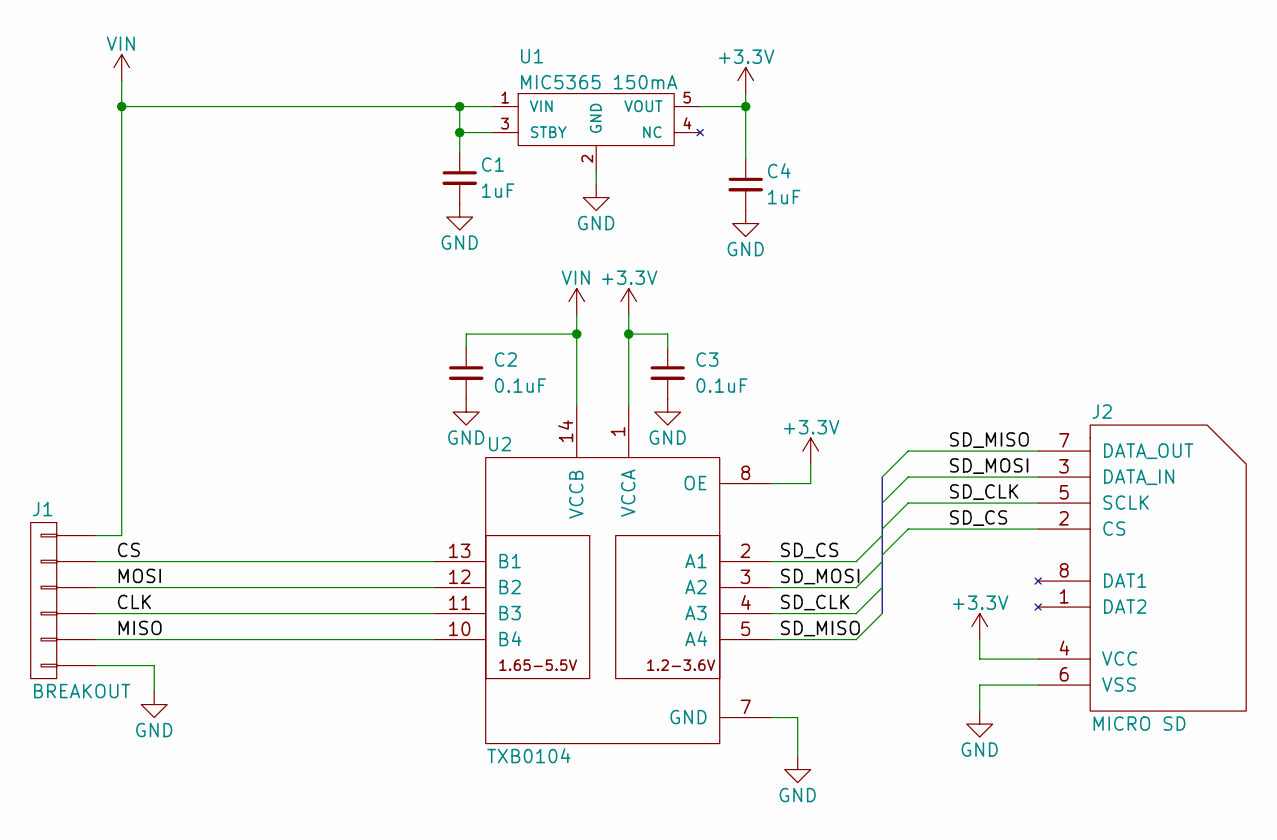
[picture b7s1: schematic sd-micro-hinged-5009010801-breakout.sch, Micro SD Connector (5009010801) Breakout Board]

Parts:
C1, C4: 1uF; RLC-0603-SMD
C2, C3: 0.1uF; RLC-0603-SMD
J1: BREAKOUT; CONN-HEADER-STRAIGHT-P2.54MM-1x06
J2: MICRO SD; CONN-SD-MICRO-MOLEX-5009010801
U1: MIC5365 150mA; SOT-353
U2: TXB0104; SOIC-14-3.9x8.7MM-P1.27MM

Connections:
+3V3: C3.1, C4.1, J2.4 (VCC), U1.5 (VOUT), U2.1 (VCCA), U2.8 (OE)
/CLK: J1.4, U2.11 (B3)
/CS: J1.2, U2.13 (B1)
/MISO: J1.5, U2.10 (B4)
/MOSI: J1.3, U2.12 (B2)
/SD_CLK: J2.5 (SCLK), U2.4 (A3)
/SD_CS: J2.2 (CS), U2.2 (A1)
/SD_MISO: J2.7 (DATA_OUT), U2.5 (A4)
/SD_MOSI: J2.3 (DATA_IN), U2.3 (A2)
GND: C1.2, C2.2, C3.2, C4.2, J1.6, J2.6 (VSS), U1.2 (GND), U2.7 (GND)
VIN: C1.1, C2.1, J1.1, U1.1 (VIN), U1.3 (STBY), U2.14 (VCCB)

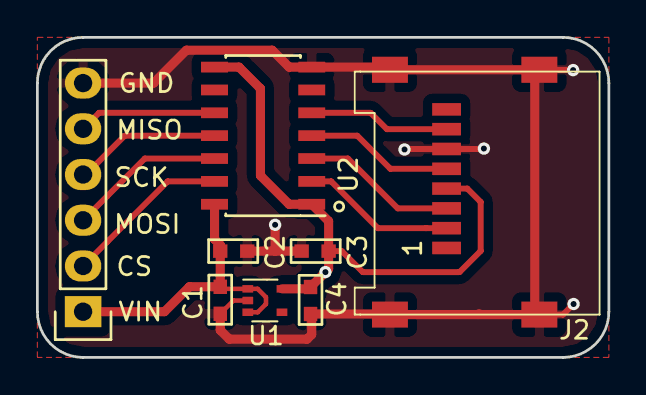
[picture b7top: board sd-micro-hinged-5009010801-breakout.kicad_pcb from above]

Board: 2 copper layers, 31.8 x 17.8 mm, 8 parts (0 on the bottom side), 11 nets.
